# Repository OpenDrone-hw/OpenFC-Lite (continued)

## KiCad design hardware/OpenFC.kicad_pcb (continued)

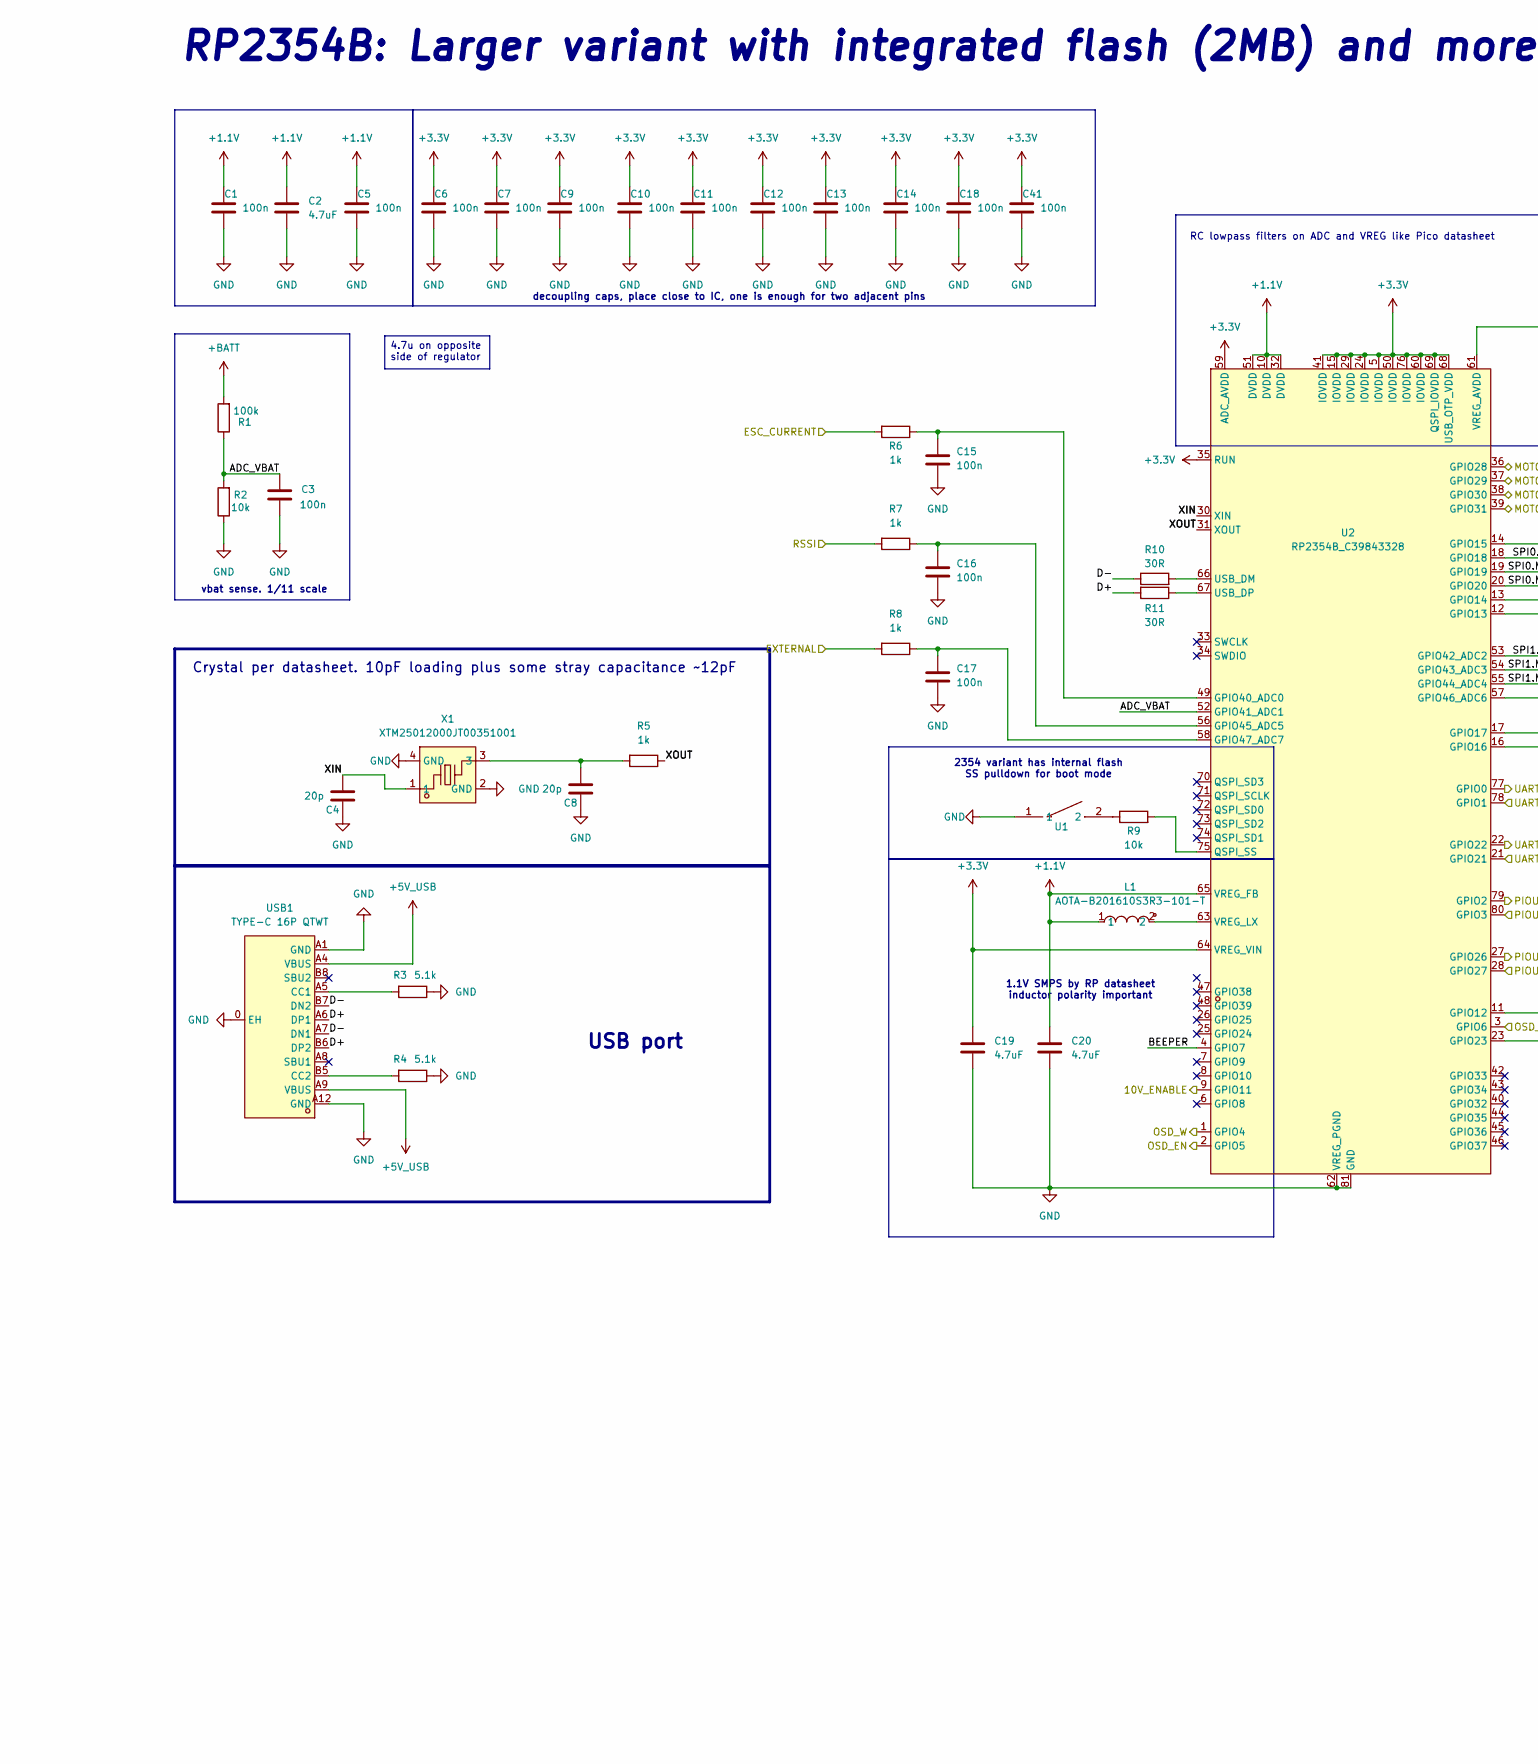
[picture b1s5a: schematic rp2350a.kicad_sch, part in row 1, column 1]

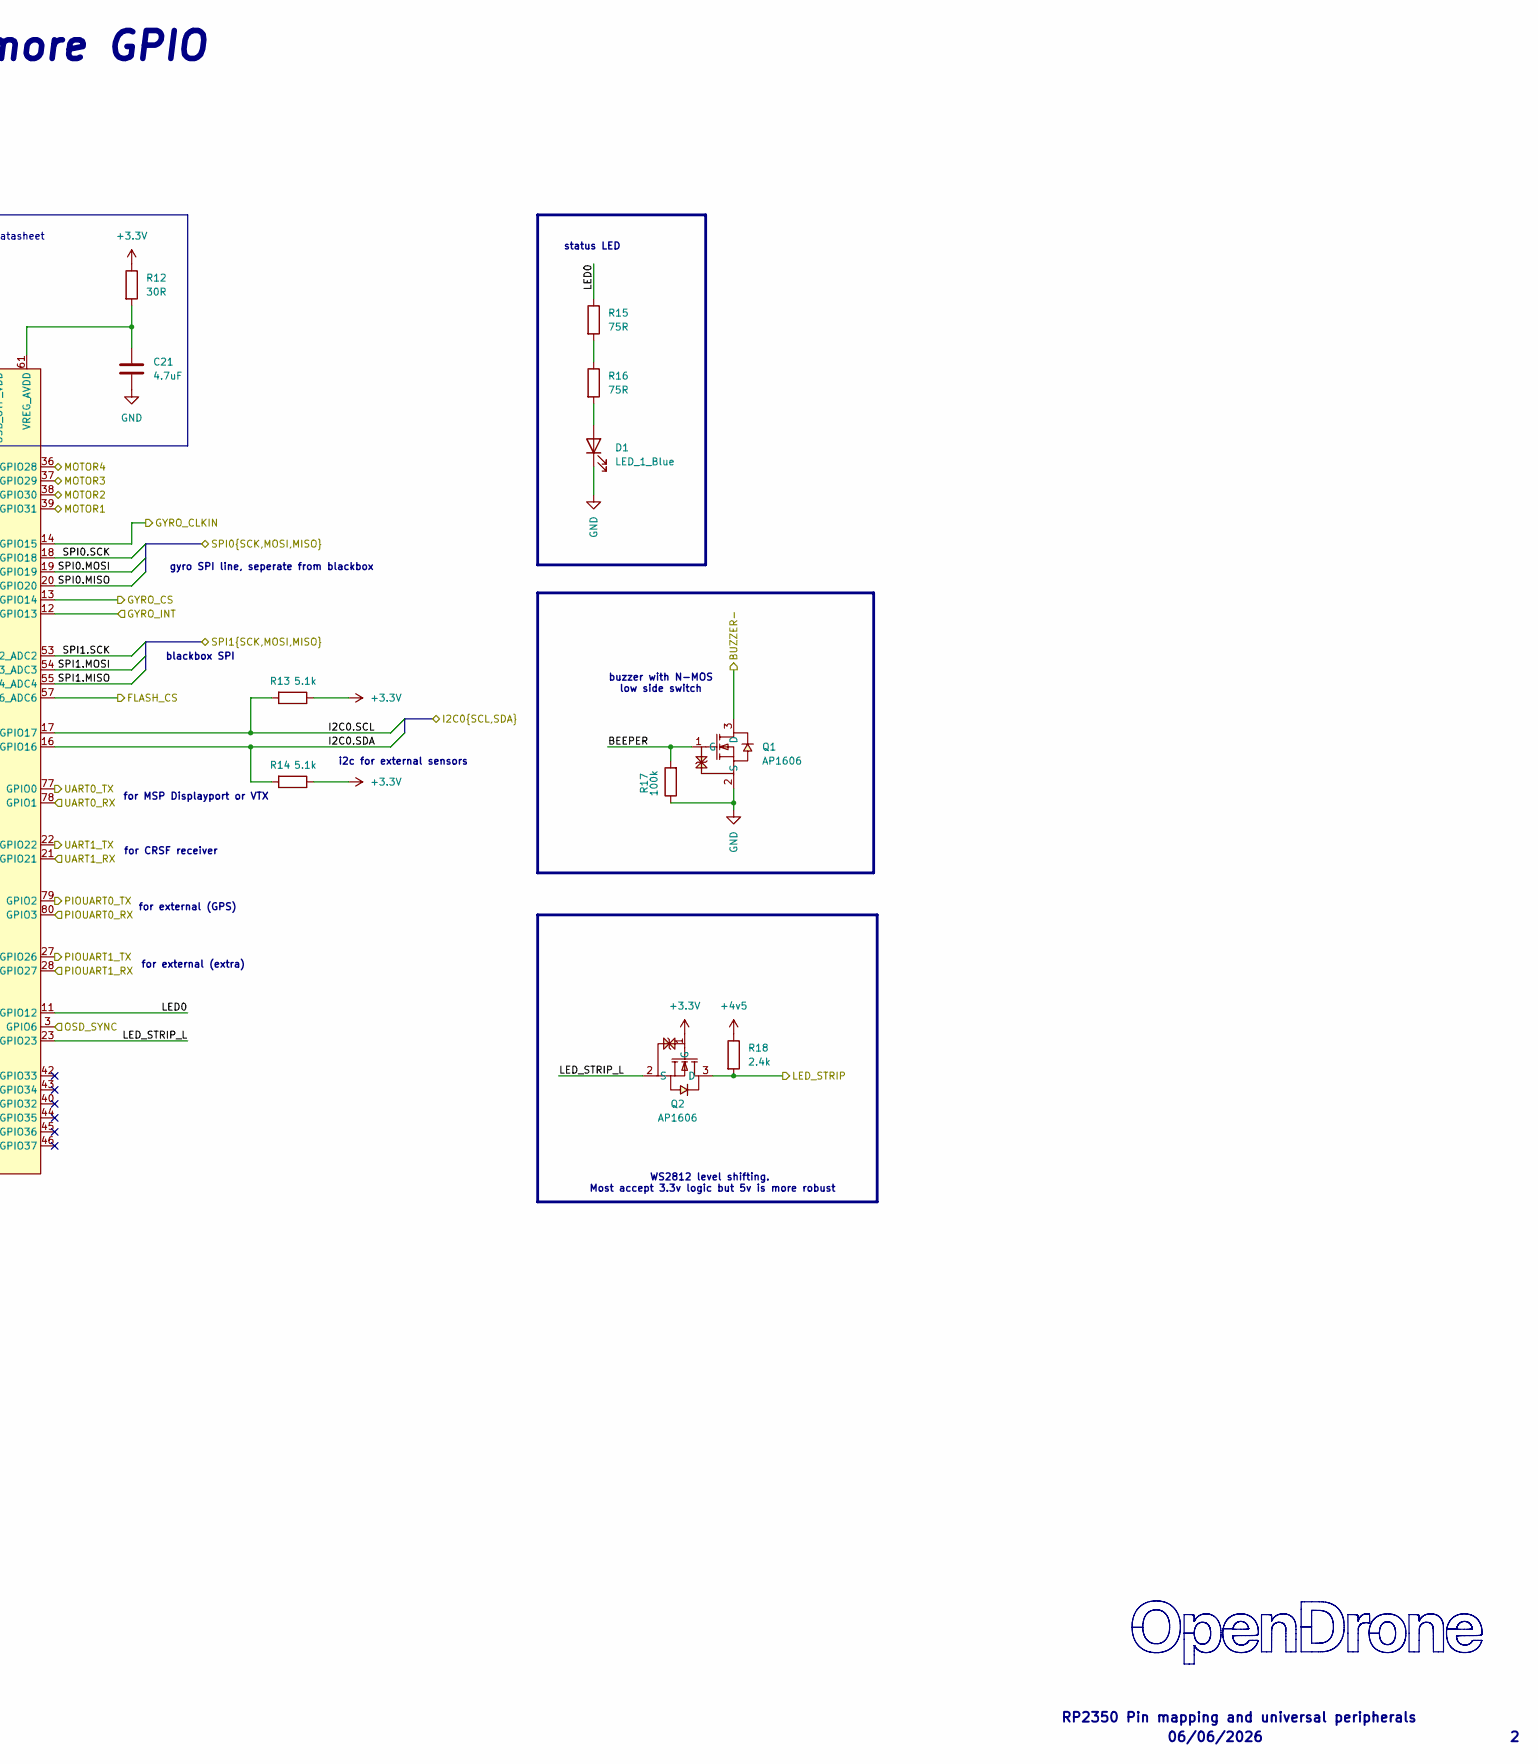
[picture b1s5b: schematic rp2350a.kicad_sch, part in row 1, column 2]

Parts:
C1, C3, C5, C6, C7, C9, C10, C11, C12, C13, C14, C15, C16, C17, C18, C41: 100n; C_0201_0603Metric; MPN GRM033R61E104KE14D; LCSC C76939
C2, C19, C20, C21: 4.7uF; C_0402_1005Metric; MPN CL05A475MP5NRNC; LCSC C23733
C4, C8: 20p; C_0201_0603Metric; MPN GRM0335C1H200JA01D; LCSC C76923
D1: LED_1_Blue; LED_0402_1005Metric; MPN XL-1005UBC; LCSC C22355736
L1: AOTA-B201610S3R3-101-T; IND-SMD_L2.0-W1.6_AOTA-B201610S3R3-101-T; MPN AOTA-B201610S3R3-101-T; LCSC C42411119
Q1, Q2: AP1606; DFN-3L_L1.0-W0.6-P0.65-BR; MPN AP1606; LCSC C2849580
R1, R17: 100k; R_0201_0603Metric; MPN 0201WMF1003TEE; LCSC C270364
R2, R9: 10k; R_0201_0603Metric; MPN RC0201FR-0710KL; LCSC C106225
R3, R4, R13, R14: 5.1k; R_0201_0603Metric; MPN 0201WMF5101TEE; LCSC C270344
R5, R6, R7, R8: 1k; R_0201_0603Metric; MPN 0201WMF1001TEE; LCSC C270365
R10, R11, R12: 30R; R_0201_0603Metric; MPN NQ01WMJ0300TEE; LCSC C778391
R15, R16: 75R; R_0201_0603Metric; MPN RC0201FR-0775RL; LCSC C274878
R18: 2.4k; R_0201_0603Metric; MPN RTT012401FTH; LCSC C166281
U1: TS2306A 240GF MSM 9_C2976675; SW-SMD_4P-L3.0-W2.0-P0.85-LS3.5; MPN TS2306A 240gf MSM 9; LCSC C2976675
U2: RP2354B_C39843328; QFN-80_L10.0-W10.0-P0.40-TL-EP3.4; MPN RP2354B; LCSC C39843328
USB1: TYPE-C 16P QTWT; USB-TYPE-C-SMD_TYPE-C-16P-QTWT; MPN TYPE-C 16P QTWT; LCSC C5187472
X1: XTM25012000JT00351001; CRYSTAL-SMD_4P-L2.5-W2.0-BL-A; MPN XTM25012000JT00351001; LCSC C37635340

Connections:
+1.1V: C1.1, C2.1, C5.1, C20.1, L1.1, U2.10 (DVDD), U2.32 (DVDD), U2.51 (DVDD), U2.65 (VREG_FB)
+3.3V: C6.1, C7.1, C9.1, C10.1, C11.1, C12.1, C13.1, C14.1, C18.1, C19.1, C41.1, Q2.1 (G), R12.1, R13.1, R14.1, U2.5 (IOVDD), U2.15 (IOVDD), U2.24 (IOVDD), U2.29 (IOVDD), U2.35 (RUN), U2.41 (IOVDD), U2.50 (IOVDD), U2.59 (ADC_AVDD), U2.60 (IOVDD), U2.64 (VREG_VIN), U2.68 (USB_OTP_VDD), U2.69 (QSPI_IOVDD), U2.76 (IOVDD); also elsewhere on the board
+4v5: R18.1; also elsewhere on the board
+5V_USB: USB1.A4 (VBUS), USB1.A9 (VBUS); also elsewhere on the board
+BATT: R1.2; also elsewhere on the board
/BLACKBOX/FLASH_CS: U2.57 (GPIO46_ADC6); also elsewhere on the board
/BLACKBOX/SPI1.MISO: U2.55 (GPIO44_ADC4); also elsewhere on the board
/BLACKBOX/SPI1.MOSI: U2.54 (GPIO43_ADC3); also elsewhere on the board
/BLACKBOX/SPI1.SCK: U2.53 (GPIO42_ADC2); also elsewhere on the board
/IMU/CLKIN: U2.14 (GPIO15); also elsewhere on the board
/IMU/CS: U2.13 (GPIO14); also elsewhere on the board
/IMU/GYRO_INT: U2.12 (GPIO13); also elsewhere on the board
/IMU/SPI0.MISO: U2.20 (GPIO20); also elsewhere on the board
/IMU/SPI0.MOSI: U2.19 (GPIO19); also elsewhere on the board
/IMU/SPI0.SCK: U2.18 (GPIO18); also elsewhere on the board
/OSD/OSD_EN: U2.2 (GPIO5); also elsewhere on the board
/OSD/OSD_SYNC: U2.3 (GPIO6); also elsewhere on the board
/OSD/OSD_W: U2.1 (GPIO4); also elsewhere on the board
/PADS/ADC2: R8.2; also elsewhere on the board
/PADS/BUZZER-: Q1.3 (D); also elsewhere on the board
/PADS/CURRENT: R6.2; also elsewhere on the board
/PADS/I2C0.SCL: R13.2, U2.17 (GPIO17); also elsewhere on the board
/PADS/I2C0.SDA: R14.2, U2.16 (GPIO16); also elsewhere on the board
/PADS/LED_STRIP: Q2.3 (D), R18.2; also elsewhere on the board
/PADS/M1: U2.39 (GPIO31); also elsewhere on the board
/PADS/M2: U2.38 (GPIO30); also elsewhere on the board
/PADS/M3: U2.37 (GPIO29); also elsewhere on the board
/PADS/M4: U2.36 (GPIO28); also elsewhere on the board
/PADS/PIOUART0_RX: U2.80 (GPIO3); also elsewhere on the board
/PADS/PIOUART0_TX: U2.79 (GPIO2); also elsewhere on the board
/PADS/PU1RX: U2.28 (GPIO27); also elsewhere on the board
/PADS/PU1TX: U2.27 (GPIO26); also elsewhere on the board
/PADS/RSSI: R7.2; also elsewhere on the board
/PADS/U1RX: U2.21 (GPIO21); also elsewhere on the board
/PADS/UART0_RX: U2.78 (GPIO1); also elsewhere on the board
/PADS/UART0_TX: U2.77 (GPIO0); also elsewhere on the board
/PADS/UART1_TX: U2.22 (GPIO22); also elsewhere on the board
/POWER/10V_ENABLE: U2.9 (GPIO11); also elsewhere on the board
/RP2350A/ADC_VBAT: C3.2, R1.1, R2.2, U2.52 (GPIO41_ADC1)
/RP2350A/BEEPER: Q1.1 (G), R17.2, U2.4 (GPIO7)
/RP2350A/D+: R11.2, USB1.A6 (DP1), USB1.B6 (DP2)
/RP2350A/D-: R10.1, USB1.A7 (DN1), USB1.B7 (DN2)
/RP2350A/LED0: R15.1, U2.11 (GPIO12)
/RP2350A/LED_STRIP_L: Q2.2 (S), U2.23 (GPIO23)
/RP2350A/XIN: C4.2, U2.30 (XIN), X1.1
/RP2350A/XOUT: R5.1, U2.31 (XOUT)
GND: C1.2, C2.2, C3.1, C4.1, C5.2, C6.2, C7.2, C8.1, C9.2, C10.2, C11.2, C12.2, C13.2, C14.2, C15.2, C16.2, C17.2, C18.2, C19.2, C20.2, C21.2, C41.2, D1.1 (K), Q1.2 (S), R2.1, R3.1, R4.1, R17.1, U1.1, U2.62 (VREG_PGND), U2.81 (GND), USB1.0 (EH), USB1.A1 (GND), USB1.A12 (GND), X1.2 (GND), X1.4 (GND); also elsewhere on the board
unnamed: C8.2, R5.2, X1.3
unnamed: D1.2 (A), R16.2
unnamed: R9.1, U1.2
unnamed: R15.2, R16.1
unnamed: C15.1, R6.1, U2.49 (GPIO40_ADC0)
unnamed: C16.1, R7.1, U2.56 (GPIO45_ADC5)
unnamed: C17.1, R8.1, U2.58 (GPIO47_ADC7)
unnamed: R9.2, U2.75 (QSPI_SS)
unnamed: R10.2, U2.66 (USB_DM)
unnamed: R11.1, U2.67 (USB_DP)
unnamed: C21.1, R12.2, U2.61 (VREG_AVDD)
unnamed: L1.2, U2.63 (VREG_LX)
unnamed: R3.2, USB1.A5 (CC1)
unnamed: R4.2, USB1.B5 (CC2)

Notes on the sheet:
RP2350 Pin mapping and universal peripherals
vbat sense. 1/11 scale
RP2354B: Larger variant with integrated flash (2MB) and more GPIO
blackbox SPI
06/06/2026
for MSP Displayport or VTX
2354 variant has internal flash SS pulldown for boot mode
for CRSF receiver
gyro SPI line, seperate from blackbox
decoupling caps, place close to IC, one is enough for two adjacent pins
for external (extra)
Crystal per datasheet. 10pF loading plus some stray capacitance ~12pF
for external (GPS)
i2c for external sensors
WS2812 level shifting. Most accept 3.3v logic but 5v is more robust
status LED
RC lowpass filters on ADC and VREG like Pico datasheet
USB port
1.1V SMPS by RP datasheet inductor polarity important
buzzer with N-MOS low side switch
4.7u on opposite side of regulator

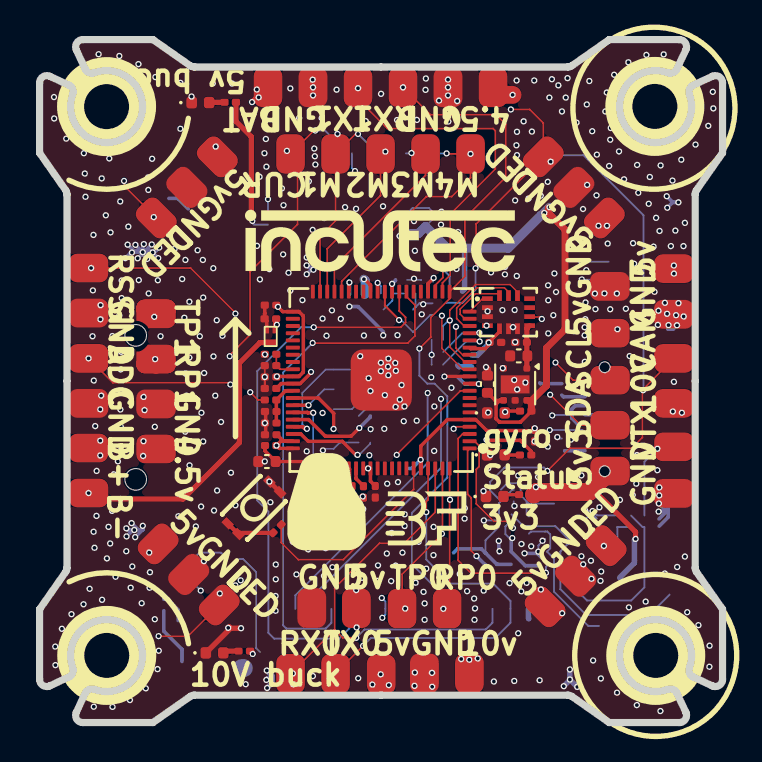
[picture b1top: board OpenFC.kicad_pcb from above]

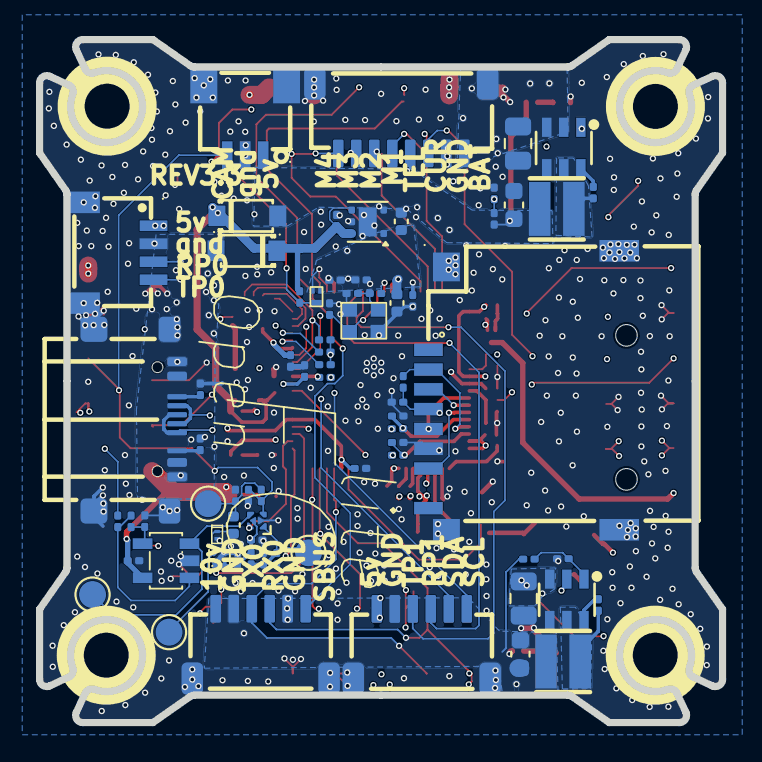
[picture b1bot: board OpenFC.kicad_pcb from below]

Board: 6 copper layers, 37.9 x 37.9 mm, 164 parts (72 on the bottom side), 82 nets.

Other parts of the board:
C35: 100n; C_0201_0603Metric
Card1: TF PUSH; TF-SMD_TF-PUSH
R30: 10k; R_0201_0603Metric

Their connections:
+3.3V: C35.1, Card1.4 (VDD), R30.1; also elsewhere on the board
/BLACKBOX/FLASH_CS: Card1.2 (CD/DAT3), R30.2; also elsewhere on the board
/BLACKBOX/SPI1.MISO: Card1.7 (DAT0); also elsewhere on the board
/BLACKBOX/SPI1.MOSI: Card1.3 (CMD); also elsewhere on the board
/BLACKBOX/SPI1.SCK: Card1.5 (CLX); also elsewhere on the board
GND: C35.2, Card1.6 (VSS), Card1.10, Card1.11, Card1.12, Card1.13; also elsewhere on the board

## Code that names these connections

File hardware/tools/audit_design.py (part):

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    # ---- 3. Power tree ----
    W("## 3. Power Tree\n")
    W("```")
    W("+BATT -> U6 (LMR51420YFDDCR buck) -> +12V   [switchable via GPIO11 via Q?]")
    W("+BATT -> U7 (LMR51420YFDDCR buck) -> +5V_BUCK")
    W("+5V_BUCK -+")
    W("          +- U33 (TPS2116 mux) -> +5V")
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                     ", ".join(caps) or "**NONE**"])
    W(md_table(["Role", "Net", "MCU pad", "Resistors on net", "Bypass caps to GND"], rows))
    W("")
    W("**Check**: A CURRENT-sense ADC input WITHOUT a bypass cap at the MCU pin is a "
      "Betaflight MFG-guideline violation (noise couples straight into ADC).\n")

    # ---- 6. SPI buses & CS pull-ups ----
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    W("## 15. CLAUDE.md GPIO map cross-check\n")
    # From CLAUDE.md
    claude_gpio = {
        "GPIO0":  "UART0 TX",
        "GPIO1":  "UART0 RX",
        "GPIO2":  "PIO UART0 TX",
        "GPIO3":  "PIO UART0 RX",
        "GPIO6":  "Beeper",
        "GPIO11": "10V enable",
        "GPIO12": "Status LED",
        "GPIO13": "IMU INT",
        "GPIO14": "IMU CS",
        "GPIO18": "IMU SCK",
        "GPIO19": "IMU MISO",
        "GPIO20": "IMU MOSI",
        "GPIO21": "UART1 RX",
        "GPIO22": "UART1 TX",
        "GPIO23": "LED strip",
        "GPIO26": "PIO UART1 TX",
        "GPIO27": "PIO UART1 RX",
        "GPIO28": "M4",
        "GPIO29": "M3",
        "GPIO30": "M2",
        "GPIO31": "M1",
        "GPIO32": "OSD VBLACK",
        "GPIO33": "OSD SYNC_IN",
        "GPIO34": "OSD PIXEL_SEL",
        "GPIO35": "OSD VWHITE",
        "GPIO36": "OSD COLOR_SEL",
        "GPIO37": "OSD SYNCLVL",
        "GPIO40": "CURRENT ADC",
        "GPIO41": "VBAT ADC",
        "GPIO45": "RSSI ADC",
        "GPIO47": "EXT ADC",
    }
    # Build GPIO# -> (pad, net) map from U36 pin functions
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        cn = curr_candidates[0]
        caps = find_caps_between({}, net2rp, cn, "GND")
        if not caps:
            findings.append(("HIGH", f"CURRENT-sense net `{cn}` has NO bypass cap to GND, add ~100nF near MCU ADC pin."))
    # VBAT bypass
    vb_candidates = [n for n in net2rp if re.search(r"VBAT.*SENSE|VBAT_?ADC", n, re.I)]
    if vb_candidates:
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
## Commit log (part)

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2026-06-17 Re-route with connectors
